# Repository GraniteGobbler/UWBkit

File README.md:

# UWBkit

This is a repository containing firmware from two other repositories and is released under their license:
- [DWM3001C-starter-firmware](https://github.com/Uberi/DWM3001C-starter-firmware), by Uberi (as of [02c341b](https://github.com/Uberi/DWM3001C-starter-firmware/commit/02c341b4f58dd8410239b5278b40aece675a3650))
- [SSD1306-LCD-on-NRF52](https://github.com/jimmywong2003/SSD1306-LCD-on-NRF52), by jimmywong2003 (as of [4ca746a](https://github.com/jimmywong2003/SSD1306-LCD-on-NRF52/commit/4ca746a075d3628c971d63ee42bb9b67d5787345))

All other files are released under the [Creative Commons CC0 license](https://creativecommons.org/public-domain/cc0/).

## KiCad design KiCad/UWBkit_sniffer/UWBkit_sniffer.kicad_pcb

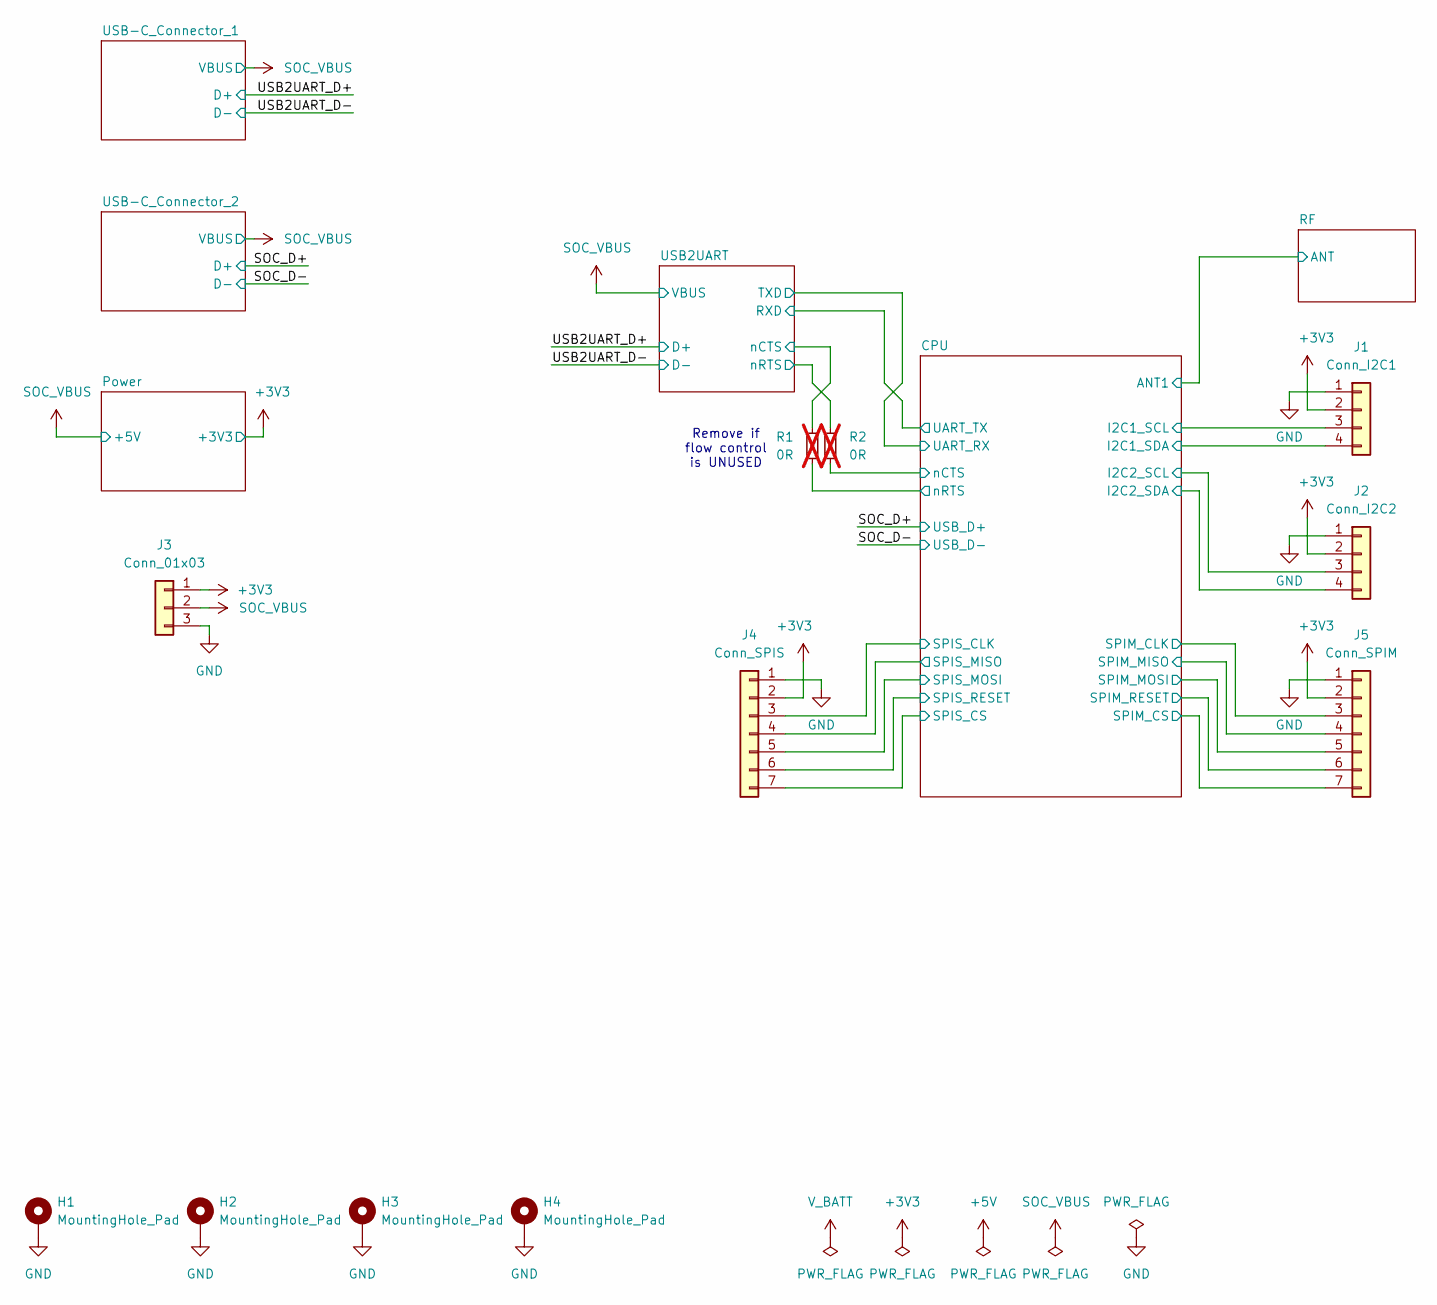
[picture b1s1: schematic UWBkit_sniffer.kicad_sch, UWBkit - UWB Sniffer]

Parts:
H1, H2, H3, H4: MountingHole_Pad; MountingHole_3.2mm_M3_Pad_Via
J1: Conn_I2C1; PinSocket_1x04_P2.54mm_Vertical
J2: Conn_I2C2; PinSocket_1x04_P2.54mm_Vertical
J3: Conn_01x03; PinSocket_1x03_P2.54mm_Vertical
J4: Conn_SPIS; PinSocket_1x07_P2.54mm_Vertical
J5: Conn_SPIM; PinSocket_1x07_P2.54mm_Vertical
R1, R2: 0R; R_0603_1608Metric; not fitted

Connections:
+3V3: J1.2, J2.2, J3.1, J4.2, J5.2; also elsewhere on the board
/CPU/I2C1_SCL: J1.3; also elsewhere on the board
/CPU/I2C1_SDA: J1.4; also elsewhere on the board
/CPU/I2C2_SCL: J2.3; also elsewhere on the board
/CPU/I2C2_SDA: J2.4; also elsewhere on the board
/CPU/SPIM_CLK: J5.3; also elsewhere on the board
/CPU/SPIM_CS: J5.7; also elsewhere on the board
/CPU/SPIM_MISO: J5.4; also elsewhere on the board
/CPU/SPIM_MOSI: J5.5; also elsewhere on the board
/CPU/SPIM_RESET: J5.6; also elsewhere on the board
/CPU/SPIS_CLK: J4.3; also elsewhere on the board
/CPU/SPIS_CS: J4.7; also elsewhere on the board
/CPU/SPIS_MISO: J4.4; also elsewhere on the board
/CPU/SPIS_MOSI: J4.5; also elsewhere on the board
/CPU/SPIS_RESET: J4.6; also elsewhere on the board
/CPU/nCTS: R2.2; also elsewhere on the board
/CPU/nRTS: R1.2; also elsewhere on the board
/USB2UART/nCTS: R1.1; also elsewhere on the board
/USB2UART/nRTS: R2.1; also elsewhere on the board
GND: H1.1, H2.1, H3.1, H4.1, J1.1, J2.1, J3.3, J4.1, J5.1; also elsewhere on the board
SOC_VBUS: J3.2; also elsewhere on the board

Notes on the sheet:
Remove if flow control is UNUSED

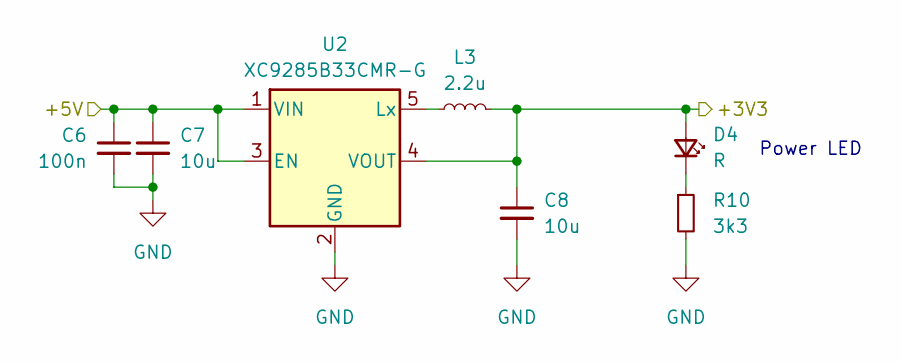
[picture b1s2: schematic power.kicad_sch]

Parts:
C6: 100n; C_0603_1608Metric
C7, C8: 10u; C_0603_1608Metric
D4: R; LED_0603_1608Metric; Voltage 1.75 V
L3: 2.2u; L_0805_2012Metric
R10: 3k3; R_0603_1608Metric
U2: XC9285B33CMR-G; SOT-23-5

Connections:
+3V3: C8.1, D4.2 (A), L3.2, U2.4 (VOUT); also elsewhere on the board
GND: C6.2, C7.2, C8.2, R10.2, U2.2 (GND); also elsewhere on the board
unnamed: D4.1 (K), R10.1
unnamed: L3.1, U2.5 (Lx)
SOC_VBUS: C6.1, C7.1, U2.1 (VIN), U2.3 (EN); also elsewhere on the board

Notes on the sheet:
Power LED

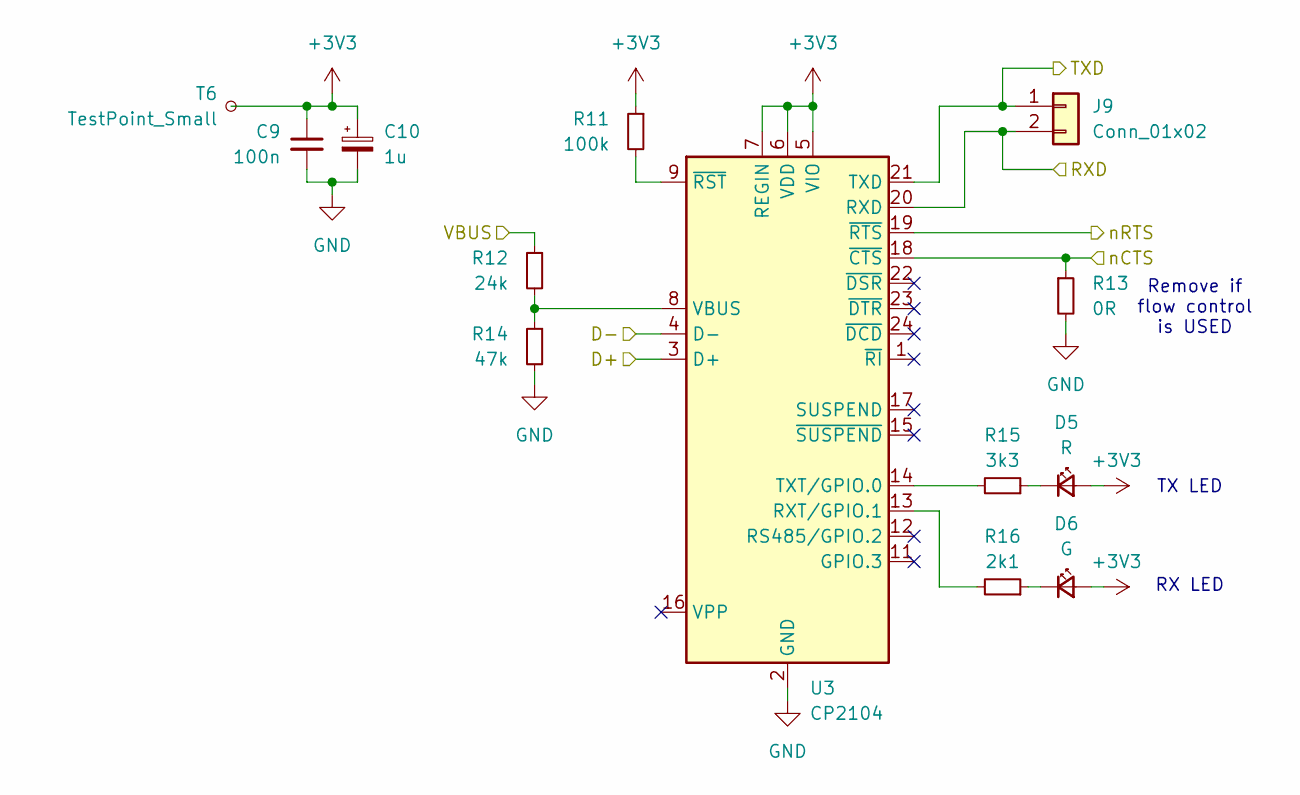
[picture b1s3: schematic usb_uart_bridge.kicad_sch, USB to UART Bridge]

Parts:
C9: 100n; C_0603_1608Metric
C10: 1u; CP_EIA-3216-18_Kemet-A
D5: R; LED_0603_1608Metric; Voltage 1.75 V
D6: G; LED_0603_1608Metric; Voltage 2.25 V
J9: Conn_01x02; PinHeader_1x02_P2.54mm_Vertical
R11: 100k; R_0603_1608Metric
R12: 24k; R_0603_1608Metric
R13: 0R; R_0603_1608Metric
R14: 47k; R_0603_1608Metric
R15: 3k3; R_0603_1608Metric
R16: 2k1; R_0603_1608Metric
T6: TestPoint_Small; TestPoint_Pad_D1.0mm
U3: CP2104; QFN-24-1EP_4x4mm_P0.5mm_EP2.6x2.6mm

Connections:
+3V3: C9.1, C10.1, D5.2 (A), D6.2 (A), R11.1, T6.1, U3.5 (VIO), U3.6 (VDD), U3.7 (REGIN); also elsewhere on the board
/CPU/UART_RX: J9.1, U3.21 (TXD); also elsewhere on the board
/CPU/UART_TX: J9.2, U3.20 (RXD); also elsewhere on the board
/USB2UART/nCTS: R13.1, U3.18 (~CTS); also elsewhere on the board
/USB2UART/nRTS: U3.19 (~RTS); also elsewhere on the board
/USB2UART_D+: U3.3 (D+); also elsewhere on the board
/USB2UART_D-: U3.4 (D-); also elsewhere on the board
GND: C9.2, C10.2, R13.2, R14.2, U3.2 (GND), U3.25 (GND); also elsewhere on the board
unnamed: D5.1 (K), R15.1
unnamed: D6.1 (K), R16.1
unnamed: R16.2, U3.13 (RXT/GPIO.1)
unnamed: R15.2, U3.14 (TXT/GPIO.0)
unnamed: R12.2, R14.1, U3.8 (VBUS)
unnamed: R11.2, U3.9 (~RST)
SOC_VBUS: R12.1; also elsewhere on the board

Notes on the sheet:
Remove if flow control is USED
TX LED
RX LED

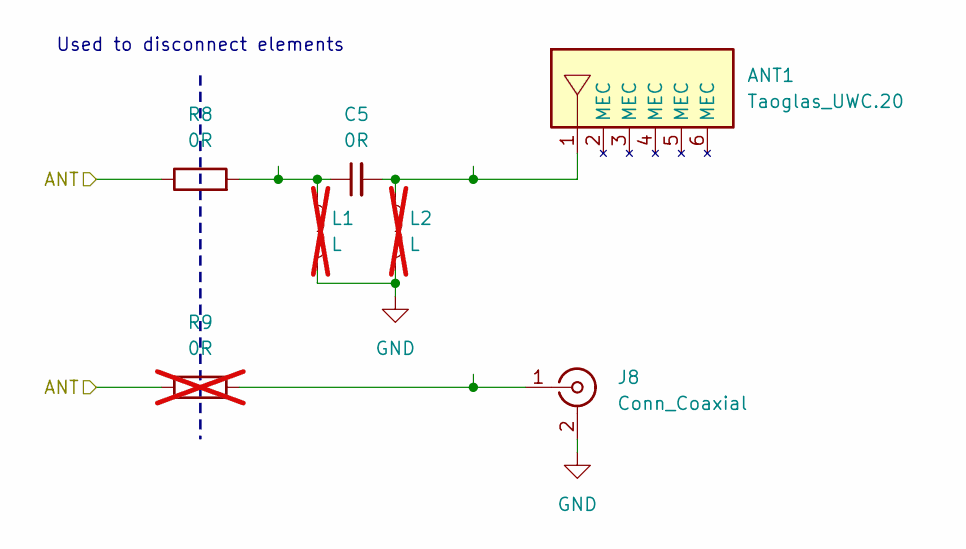
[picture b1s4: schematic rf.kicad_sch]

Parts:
ANT1: Taoglas_UWC.20
C5: 0R; C_0603_1608Metric
J8: Conn_Coaxial; SMA_Molex_73251-1153_EdgeMount_Horizontal
L1, L2: L; L_0603_1608Metric; not fitted
R8: 0R; R_0603_1608Metric
R9: 0R; R_0603_1608Metric; not fitted

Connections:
/CPU/ANT1: R8.1, R9.1; also elsewhere on the board
GND: J8.2 (Ext), L1.2, L2.2; also elsewhere on the board
unnamed: ANT1.1, C5.2, L2.1
unnamed: C5.1, L1.1, R8.2
unnamed: J8.1 (In), R9.2

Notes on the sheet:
Used to disconnect elements

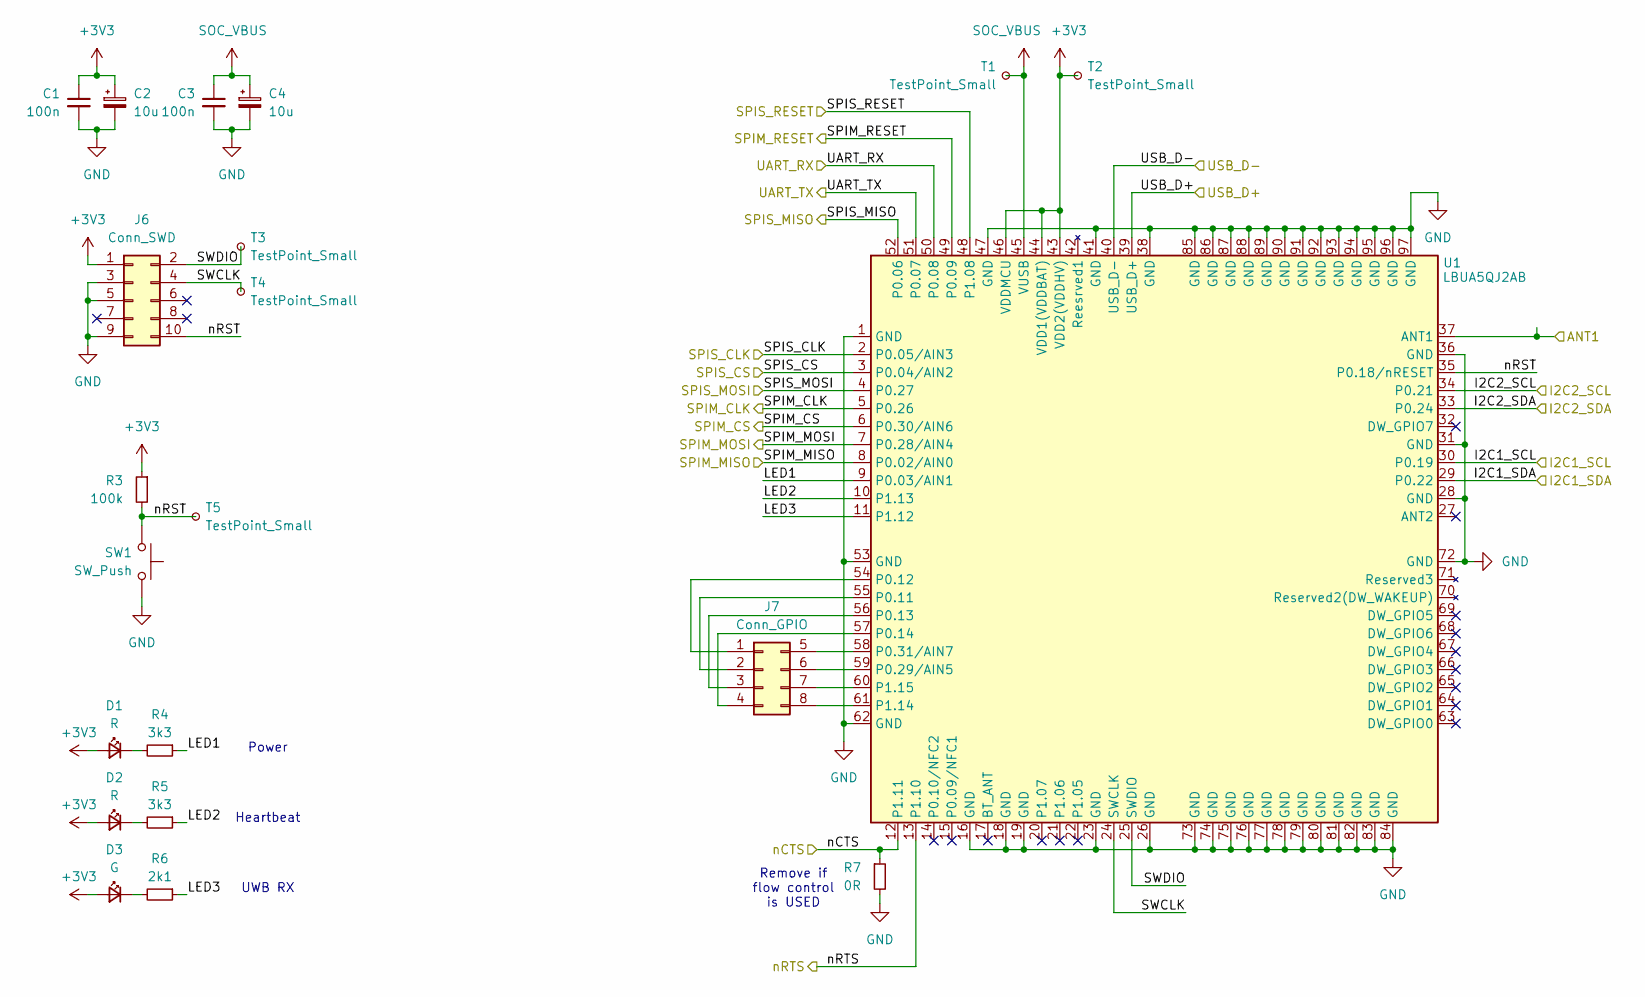
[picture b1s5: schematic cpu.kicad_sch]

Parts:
C1, C3: 100n; C_0603_1608Metric
C2, C4: 10u; CP_EIA-3216-18_Kemet-A
D1, D2: R; LED_0603_1608Metric; Voltage 1.75 V
D3: G; LED_0603_1608Metric; Voltage 2.25 V
J6: Conn_SWD; PinHeader_2x05_P1.27mm_Vertical_SMD
J7: Conn_GPIO; PinSocket_2x04_P2.54mm_Vertical
R3: 100k; R_0603_1608Metric
R4, R5: 3k3; R_0603_1608Metric
R6: 2k1; R_0603_1608Metric
R7: 0R; R_0603_1608Metric
SW1: SW_Push; SW_TH_Tactile_Omron_B3F-106x
T1, T2, T3, T4, T5: TestPoint_Small; TestPoint_Pad_D1.0mm
U1: LBUA5QJ2AB

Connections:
+3V3: C1.1, C2.1, D1.2 (A), D2.2 (A), D3.2 (A), J6.1, R3.1, T2.1, U1.43 (VDD2(VDDHV)), U1.44 (VDD1(VDDBAT)), U1.46 (VDDMCU); also elsewhere on the board
/CPU/ANT1: U1.37 (ANT1); also elsewhere on the board
/CPU/I2C1_SCL: U1.30 (P0.19); also elsewhere on the board
/CPU/I2C1_SDA: U1.29 (P0.22); also elsewhere on the board
/CPU/I2C2_SCL: U1.34 (P0.21); also elsewhere on the board
/CPU/I2C2_SDA: U1.33 (P0.24); also elsewhere on the board
/CPU/LED1: R4.1, U1.9 (P0.03/AIN1)
/CPU/LED2: R5.1, U1.10 (P1.13)
/CPU/LED3: R6.1, U1.11 (P1.12)
/CPU/SPIM_CLK: U1.5 (P0.26); also elsewhere on the board
/CPU/SPIM_CS: U1.6 (P0.30/AIN6); also elsewhere on the board
/CPU/SPIM_MISO: U1.8 (P0.02/AIN0); also elsewhere on the board
/CPU/SPIM_MOSI: U1.7 (P0.28/AIN4); also elsewhere on the board
/CPU/SPIM_RESET: U1.49 (P0.09); also elsewhere on the board
/CPU/SPIS_CLK: U1.2 (P0.05/AIN3); also elsewhere on the board
/CPU/SPIS_CS: U1.3 (P0.04/AIN2); also elsewhere on the board
/CPU/SPIS_MISO: U1.52 (P0.06); also elsewhere on the board
/CPU/SPIS_MOSI: U1.4 (P0.27); also elsewhere on the board
/CPU/SPIS_RESET: U1.48 (P1.08); also elsewhere on the board
/CPU/SWCLK: J6.4, T4.1, U1.24 (SWCLK)
/CPU/SWDIO: J6.2, T3.1, U1.25 (SWDIO)
/CPU/UART_RX: U1.50 (P0.08); also elsewhere on the board
/CPU/UART_TX: U1.51 (P0.07); also elsewhere on the board
/CPU/nCTS: R7.1, U1.12 (P1.11); also elsewhere on the board
/CPU/nRST: J6.10, R3.2, SW1.2, T5.1, U1.35 (P0.18/nRESET)
/CPU/nRTS: U1.13 (P1.10); also elsewhere on the board
/SOC_D+: U1.39 (USB_D+); also elsewhere on the board
/SOC_D-: U1.40 (USB_D-); also elsewhere on the board
GND: C1.2, C2.2, C3.2, C4.2, J6.3, J6.5, J6.9, R7.2, SW1.1, U1.1 (GND), U1.16 (GND), U1.18 (GND), U1.19 (GND), U1.23 (GND), U1.26 (GND), U1.28 (GND), U1.31 (GND), U1.36 (GND), U1.38 (GND), U1.41 (GND), U1.47 (GND), U1.53 (GND), U1.62 (GND), U1.72 (GND), U1.73 (GND), U1.74 (GND), U1.75 (GND), U1.76 (GND), U1.77 (GND), U1.78 (GND), U1.79 (GND), U1.80 (GND), U1.81 (GND), U1.82 (GND), U1.83 (GND), U1.84 (GND), U1.85 (GND), U1.86 (GND), U1.87 (GND), U1.88 (GND), U1.89 (GND), U1.90 (GND), U1.91 (GND), U1.92 (GND), U1.93 (GND), U1.94 (GND), U1.95 (GND), U1.96 (GND), U1.97 (GND); also elsewhere on the board
unnamed: D1.1 (K), R4.2
unnamed: D2.1 (K), R5.2
unnamed: D3.1 (K), R6.2
unnamed: J7.1, U1.54 (P0.12)
unnamed: J7.2, U1.55 (P0.11)
unnamed: J7.3, U1.56 (P0.13)
unnamed: J7.4, U1.57 (P0.14)
unnamed: J7.5, U1.58 (P0.31/AIN7)
unnamed: J7.6, U1.59 (P0.29/AIN5)
unnamed: J7.7, U1.60 (P1.15)
unnamed: J7.8, U1.61 (P1.14)
SOC_VBUS: C3.1, C4.1, T1.1, U1.45 (VUSB); also elsewhere on the board

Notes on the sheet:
Power
Heartbeat
Remove if flow control is USED
UWB RX

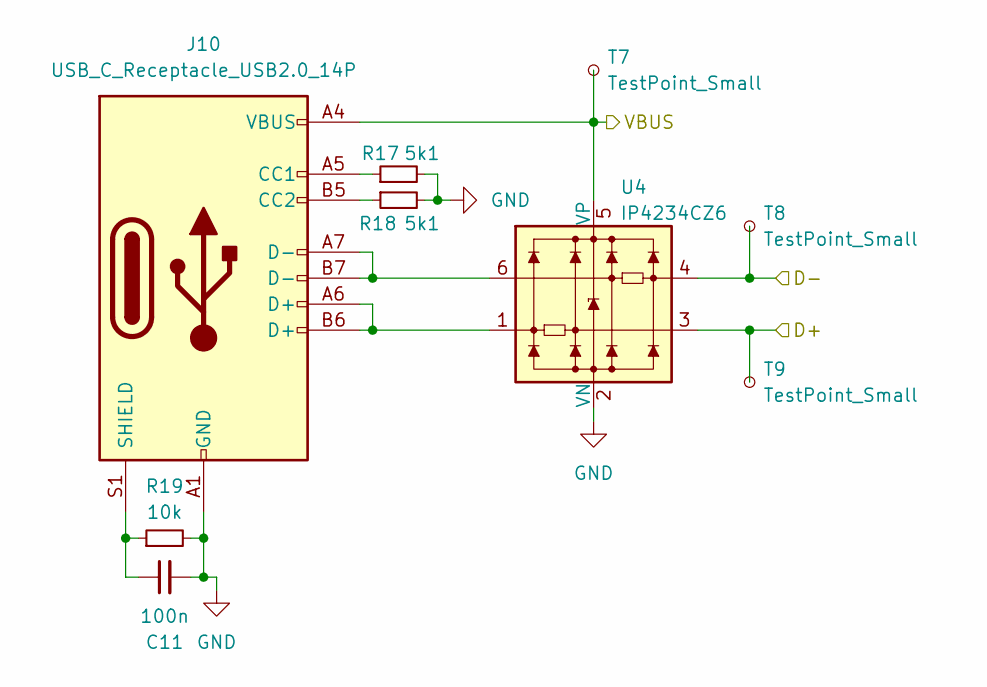
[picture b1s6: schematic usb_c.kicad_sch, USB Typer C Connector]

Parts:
C11: 100n; C_0603_1608Metric
J10: USB_C_Receptacle_USB2.0_14P; USB_C_Receptacle_GCT_USB4105-xx-A_16P_TopMnt_Horizontal
R17, R18: 5k1; R_0603_1608Metric
R19: 10k; R_0603_1608Metric
T7, T8, T9: TestPoint_Small; TestPoint_Pad_D1.0mm
U4: IP4234CZ6; SC-74-6_1.55x2.9mm_P0.95mm

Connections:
/USB2UART_D+: T9.1, U4.3; also elsewhere on the board
/USB2UART_D-: T8.1, U4.4; also elsewhere on the board
GND: C11.2, J10.A1 (GND), J10.A12 (GND), J10.B1 (GND), J10.B12 (GND), R17.2, R18.2, R19.2, U4.2 (VN); also elsewhere on the board
unnamed: J10.A5 (CC1), R17.1
unnamed: J10.B5 (CC2), R18.1
unnamed: J10.A6 (D+), J10.B6 (D+), U4.1
unnamed: J10.A7 (D-), J10.B7 (D-), U4.6
unnamed: C11.1, J10.S1 (SHIELD), R19.1
SOC_VBUS: J10.A4 (VBUS), J10.A9 (VBUS), J10.B4 (VBUS), J10.B9 (VBUS), T7.1, U4.5 (VP); also elsewhere on the board

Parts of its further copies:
C12: 100n; C_0603_1608Metric
J11: USB_C_Receptacle_USB2.0_14P; USB_C_Receptacle_GCT_USB4105-xx-A_16P_TopMnt_Horizontal
R20, R21: 5k1; R_0603_1608Metric
R22: 10k; R_0603_1608Metric
T10, T11, T12: TestPoint_Small; TestPoint_Pad_D1.0mm
U5: IP4234CZ6; SC-74-6_1.55x2.9mm_P0.95mm

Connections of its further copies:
/SOC_D+: T12.1, U5.3; also elsewhere on the board
/SOC_D-: T11.1, U5.4; also elsewhere on the board
GND: C12.2, J11.A1 (GND), J11.A12 (GND), J11.B1 (GND), J11.B12 (GND), R20.2, R21.2, R22.2, U5.2 (VN); also elsewhere on the board
unnamed: J11.A5 (CC1), R20.1
unnamed: J11.B5 (CC2), R21.1
unnamed: J11.A6 (D+), J11.B6 (D+), U5.1
unnamed: J11.A7 (D-), J11.B7 (D-), U5.6
unnamed: C12.1, J11.S1 (SHIELD), R22.1
SOC_VBUS: J11.A4 (VBUS), J11.A9 (VBUS), J11.B4 (VBUS), J11.B9 (VBUS), T10.1, U5.5 (VP); also elsewhere on the board

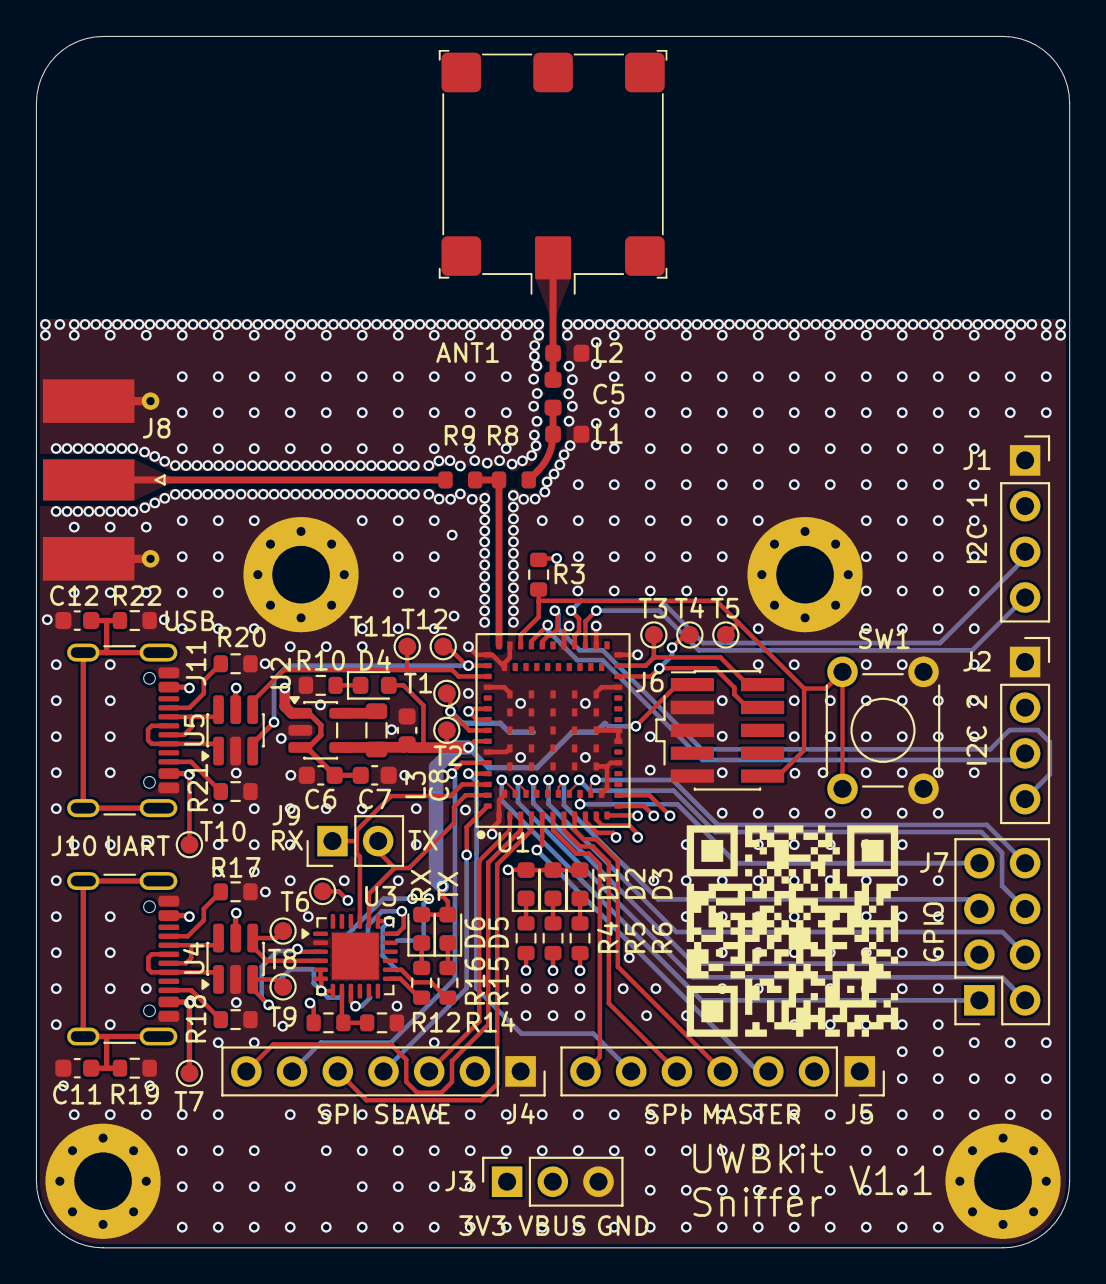
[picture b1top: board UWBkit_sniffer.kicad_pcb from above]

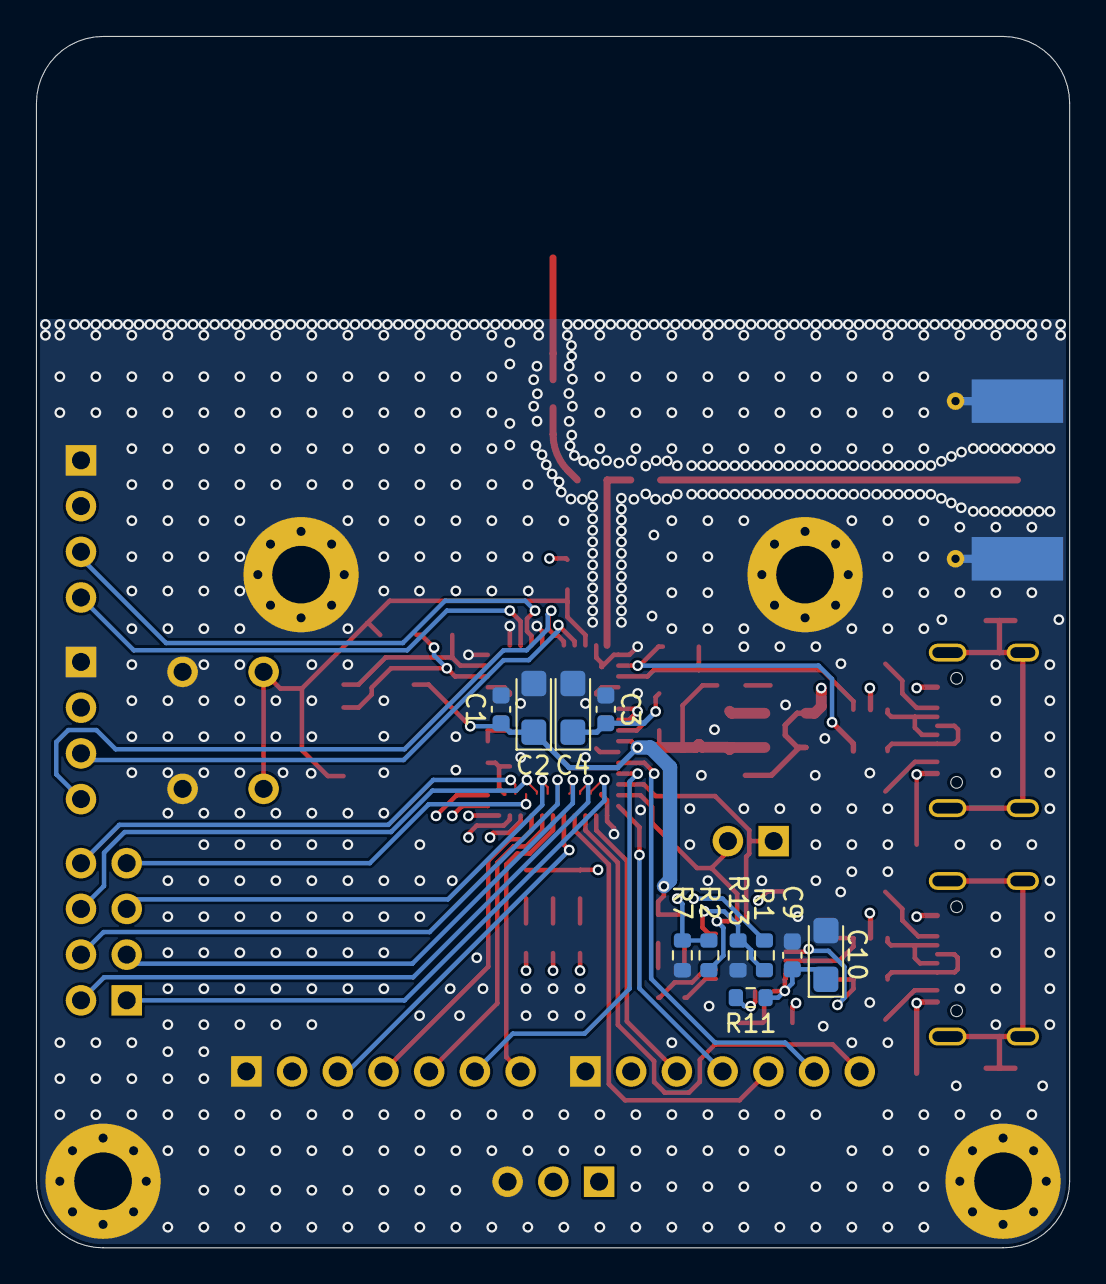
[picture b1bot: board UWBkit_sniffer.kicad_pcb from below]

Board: 4 copper layers, 57.4 x 67.3 mm, 78 parts (11 on the bottom side), 66 nets.

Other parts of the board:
QR*****: https://github.com/GraniteGobbler/UWBkit; Git-Repo-QR

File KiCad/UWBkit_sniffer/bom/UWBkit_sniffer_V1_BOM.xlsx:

Reference | Qty | Qty Owned | Qty Need | Value | Footprint |  | Mouser link
ANT1 | 1 | 0 | 1 | Taoglas_UWC.20 | UWB_Antennas:Taoglas_UWC.20 | https://cz.mouser.com/ProductDetail/Taoglas/UWC.20?qs=MLItCL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 | https://cz.mouser.com/ProductDetail/Taoglas/UWC.20?qs=MLItCL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
C1,C3,C6,C9,C11,C12 | 6 | 6 | 0 | 100n | Capacitor_SMD:C_0603_1608Metric
C2,C4 | 2 | 8 | -6 | 10u | Capacitor_Tantalum_SMD:CP_EIA-3216-18_Kemet-A
C5 | 1 | 0 | 1 | 0R | Capacitor_SMD:C_0603_1608Metric | https://cz.mouser.com/ProductDetail/Panasonic/ERJ-H3G0R00V?q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 | https://cz.mouser.com/ProductDetail/Panasonic/ERJ-H3G0R00V?q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
C7,C8 | 2 | 6 | -4 | 10u | Capacitor_SMD:C_0603_1608Metric
C10 | 1 | 0 | 1 | 1u | Capacitor_Tantalum_SMD:CP_EIA-3216-18_Kemet-A | https://cz.mouser.com/ProductDetail/KEMET/T491A105K020ATAUTO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 | https://cz.mouser.com/ProductDetail/KEMET/T491A105K020ATAUTO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
D1,D2,D4,D5 | 4 | 4 | 0 | R | LED_SMD:LED_0603_1608Metric
D3,D6 | 2 | 2 | 0 | G | LED_SMD:LED_0603_1608Metric
H1,H2,H3,H4 | 4 | 4 | 0 | MountingHole_Pad | MountingHole:MountingHole_3.2mm_M3_Pad_Via
J1 | 1 | 1 | 0 | Conn_I2C1 | Connector_PinSocket_2.54mm:PinSocket_1x04_P2.54mm_Vertical
J2 | 1 | 1 | 0 | Conn_I2C2 | Connector_PinSocket_2.54mm:PinSocket_1x04_P2.54mm_Vertical
J3 | 1 | 1 | 0 | Conn_01x03 | Connector_PinSocket_2.54mm:PinSocket_1x03_P2.54mm_Vertical
J4 | 1 | 1 | 0 | Conn_SPIS | Connector_PinSocket_2.54mm:PinSocket_1x07_P2.54mm_Vertical
J5 | 1 | 1 | 0 | Conn_SPIM | Connector_PinSocket_2.54mm:PinSocket_1x07_P2.54mm_Vertical
J6 | 1 | 0 | 1 | Conn_SWD | Connector_PinHeader_1.27mm:PinHeader_2x05_P1.27mm_Vertical_SMD | https://cz.mouser.com/ProductDetail/Samtec/FTSH-105-01-F-DV-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 | https://cz.mouser.com/ProductDetail/Samtec/FTSH-105-01-F-DV-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
J7 | 1 | 1 | 0 | Conn_GPIO | Connector_PinSocket_2.54mm:PinSocket_2x04_P2.54mm_Vertical
J8 | 1 | 0 | 1 | Conn_Coaxial | Connector_Coaxial:SMA_Molex_73251-1153_EdgeMount_Horizontal | https://cz.mouser.com/ProductDetail/Molex/73251-1153?qs=vxeU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 | https://cz.mouser.com/ProductDetail/Molex/73251-1153?qs=vxeU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
J9 | 1 | 1 | 0 | Conn_01x02 | Connector_PinHeader_2.54mm:PinHeader_1x02_P2.54mm_Vertical
J10,J11 | 2 | 1 | 1 | USB_C_Receptacle_USB2.0_14P | Connector_USB:USB_C_Receptacle_GCT_USB4105-xx-A_16P_TopMnt_Horizontal | https://cz.mouser.com/ProductDetail/GCT/USB4105-GF-A?qs=KUoI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 | https://cz.mouser.com/ProductDetail/GCT/USB4105-GF-A?qs=KUoI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
L1,L2 (DNP) | 2 | 2 | 0 | L | Inductor_SMD:L_0603_1608Metric
L3 | 1 | 8 | -7 | 2.2u | Inductor_SMD:L_0805_2012Metric
R1,R2,R9 (DNP) | 3 | 3 | 0 | 0R | Resistor_SMD:R_0603_1608Metric
R3,R11 | 2 | 15 | -13 | 100k | Resistor_SMD:R_0603_1608Metric
R4,R5,R10,R15 | 4 | 0 | 4 | 3k3 | Resistor_SMD:R_0603_1608Metric | https://cz.mouser.com/ProductDetail/YAGEO/RC0603FR-073K3L?qs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 | https://cz.mouser.com/ProductDetail/YAGEO/RC0603FR-073K3L?qs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
R6,R16 | 2 | 0 | 2 | 2k1 | Resistor_SMD:R_0603_1608Metric | https://cz.mouser.com/ProductDetail/YAGEO/RC0603FR-072K1L?qs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 | https://cz.mouser.com/ProductDetail/YAGEO/RC0603FR-072K1L?qs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
R7,R8,R13 | 3 | 3 | 0 | 0R | Resistor_SMD:R_0603_1608Metric
R12 | 1 | 0 | 1 | 24k | Resistor_SMD:R_0603_1608Metric | https://cz.mouser.com/ProductDetail/YAGEO/RC0603FR-1024KL?qs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 | https://cz.mouser.com/ProductDetail/YAGEO/RC0603FR-1024KL?qs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
R14 | 1 | 0 | 1 | 47k | Resistor_SMD:R_0603_1608Metric | https://cz.mouser.com/ProductDetail/YAGEO/AC0603FR-1347KL?qs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 | https://cz.mouser.com/ProductDetail/YAGEO/AC0603FR-1347KL?qs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
R17,R18,R20,R21 | 4 | 6 | -2 | 5k1 | Resistor_SMD:R_0603_1608Metric
R19,R22 | 2 | 8 | -6 | 10k | Resistor_SMD:R_0603_1608Metric
SW1 | 1 | 1 | 0 | SW_Push | Button_Switch_THT:SW_TH_Tactile_Omron_B3F-106x
U1 | 1 | 0 | 1 | LBUA5QJ2AB | LBUA5QJ2AB:LBUA5QJ2AB | https://cz.mouser.com/ProductDetail/Murata/LBUA5QJ2AB-828?qs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 | https://cz.mouser.com/ProductDetail/Murata/LBUA5QJ2AB-828?qs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
U2 | 1 | 0 | 1 | XC9285B33CMR-G | Package_TO_SOT_SMD:SOT-23-5 | https://cz.mouser.com/ProductDetail/Torex-Semiconductor/XC92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 | https://cz.mouser.com/ProductDetail/Torex-Semiconductor/XC92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
U3 | 1 | 0 | 1 | CP2104 | Package_DFN_QFN:QFN-24-1EP_4x4mm_P0.5mm_EP2.6x2.6mm | https://cz.mouser.com/ProductDetail/Silicon-Labs/CP2104-F03-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 | https://cz.mouser.com/ProductDetail/Silicon-Labs/CP2104-F03-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
U4,U5 | 2 | 1 | 1 | IP4234CZ6 | Package_TO_SOT_SMD:SC-74-6_1.55x2.9mm_P0.95mm | https://cz.mouser.com/ProductDetail/STMicroelectronics/USBLC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 | https://cz.mouser.com/ProductDetail/STMicroelectronics/USBLC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
0R |  |  | 7

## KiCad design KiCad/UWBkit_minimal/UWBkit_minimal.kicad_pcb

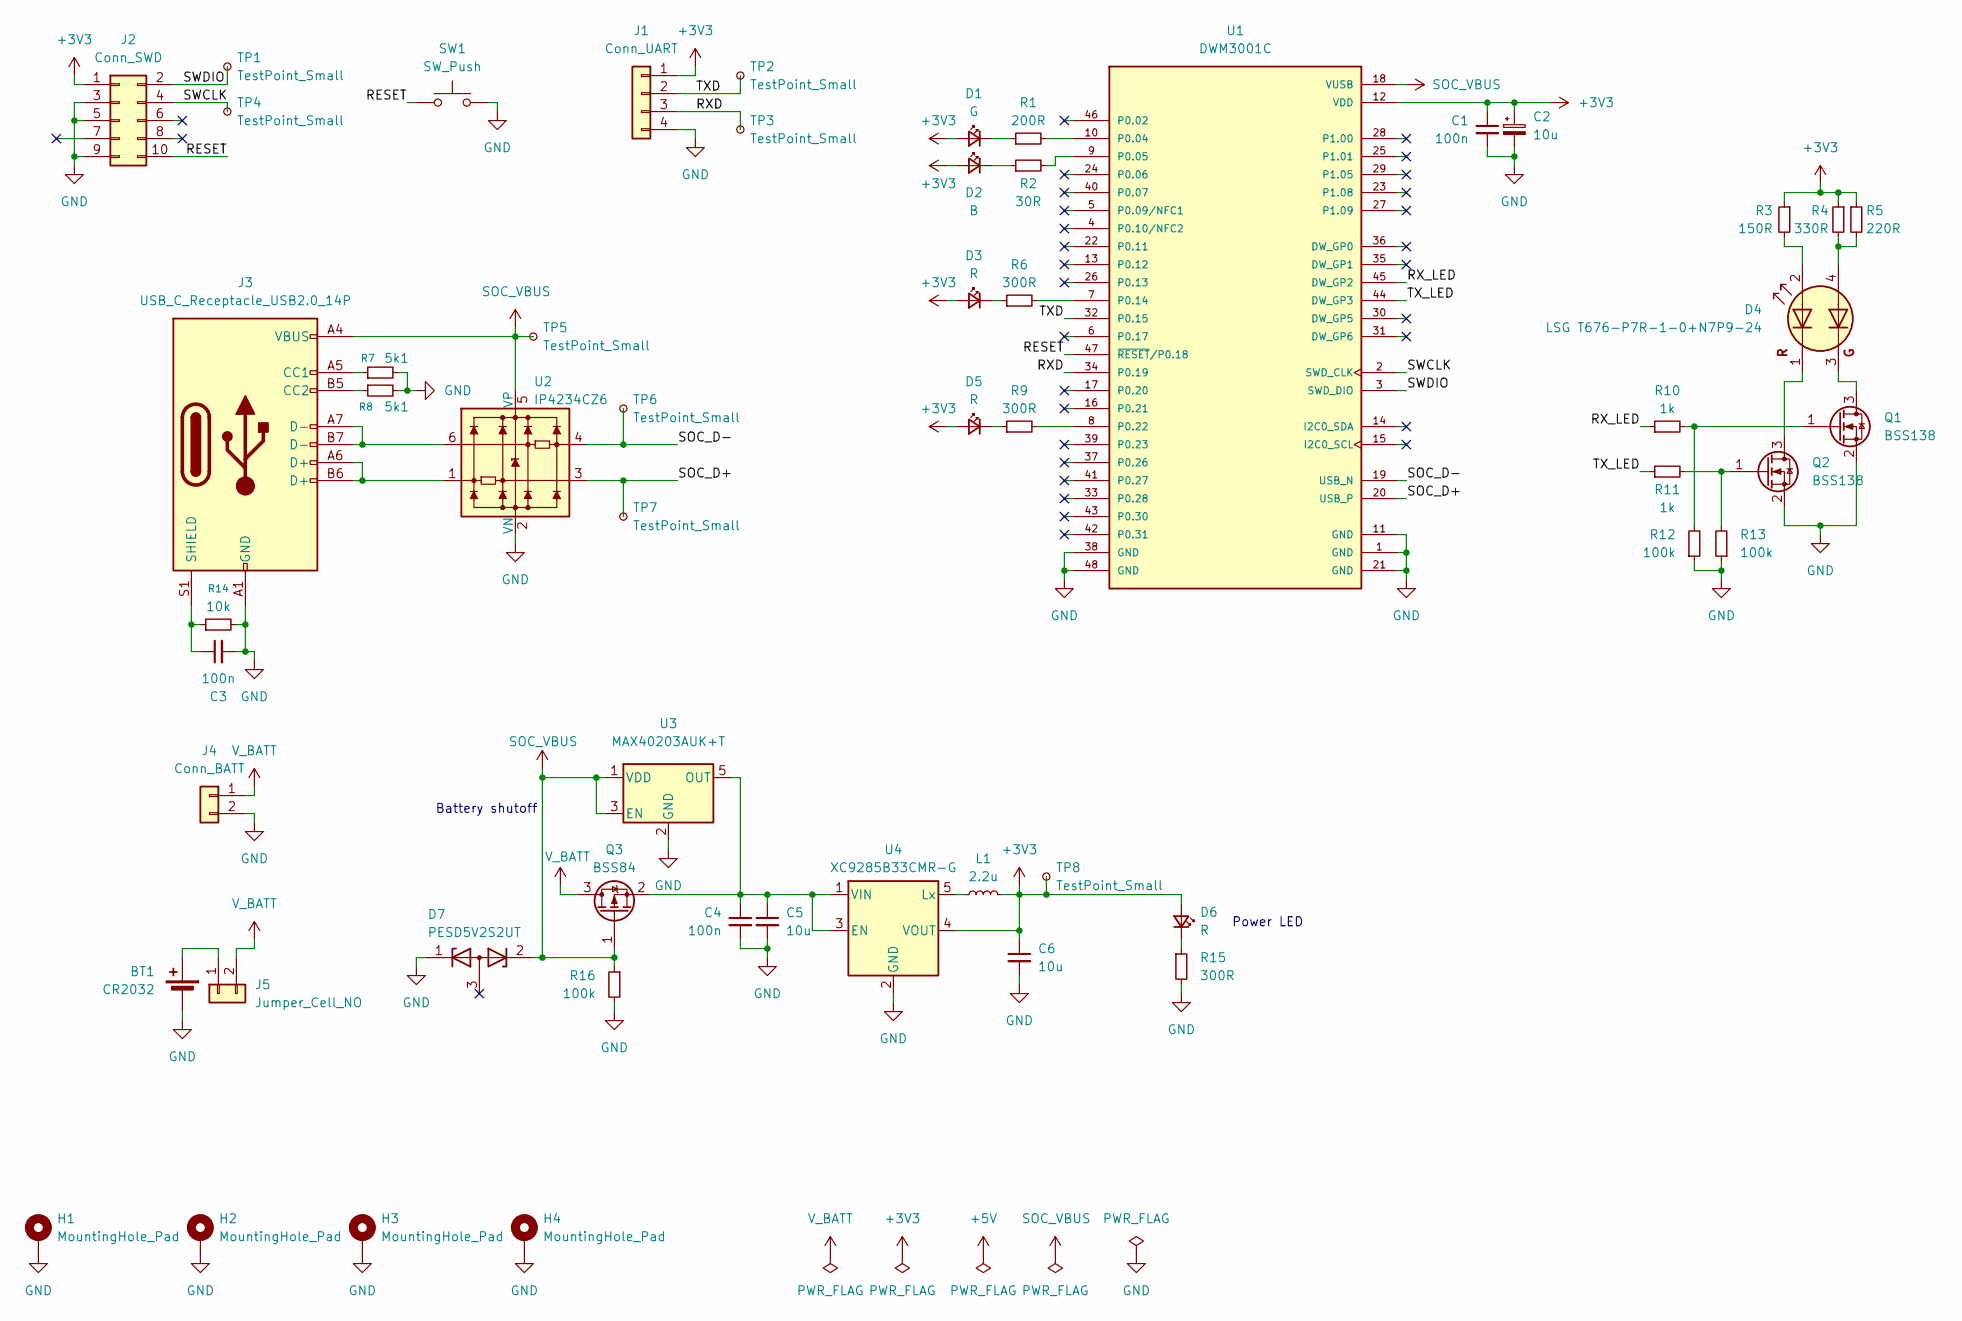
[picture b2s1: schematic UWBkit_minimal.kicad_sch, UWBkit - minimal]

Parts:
BT1: CR2032; BatteryHolder_Keystone_1058_1x2032
C1, C3, C4: 100n; C_0603_1608Metric
C2: 10u; CP_EIA-3216-18_Kemet-A
C5, C6: 10u; C_0603_1608Metric
D1: G; LED_0603_1608Metric
D2: B; LED_0603_1608Metric
D3, D5, D6: R; LED_0603_1608Metric
D4: LSG T676-P7R-1-0+N7P9-24; LED_Dual_OSRAM-PLCC4_3.2x2.8mm
D7: PESD5V2S2UT; SOT-23
H1, H2, H3, H4: MountingHole_Pad; MountingHole_3.2mm_M3_ISO14580_Pad_TopBottom
J1: Conn_UART; PinSocket_1x04_P2.54mm_Vertical
J2: Conn_SWD; PinHeader_2x05_P1.27mm_Vertical_SMD
J3: USB_C_Receptacle_USB2.0_14P; USB_C_Receptacle_GCT_USB4105-xx-A_16P_TopMnt_Horizontal
J4: Conn_BATT; PinSocket_1x02_P2.54mm_Vertical
J5: Jumper_Cell_NO; PinHeader_1x02_P2.54mm_Vertical
L1: 2.2u; L_0805_2012Metric
Q1, Q2: BSS138; SOT-23
Q3: BSS84; SOT-23-3
R1: 200R; R_0603_1608Metric
R2: 30R; R_0603_1608Metric
R3: 150R; R_0603_1608Metric
R4: 330R; R_0603_1608Metric
R5: 220R; R_0603_1608Metric
R6, R9, R15: 300R; R_0603_1608Metric
R7, R8: 5k1; R_0603_1608Metric
R10, R11: 1k; R_0603_1608Metric
R12, R13, R16: 100k; R_0603_1608Metric
R14: 10k; R_0603_1608Metric
SW1: SW_Push; SW_TH_Tactile_Omron_B3F-106x
TP1, TP4: TestPoint_Small; TestPoint_Pad_D1.5mm
TP2, TP3, TP5, TP6, TP7, TP8: TestPoint_Small; TestPoint_Pad_D1.0mm
U1: DWM3001C; PARTREV Rev C
U2: IP4234CZ6; SC-74-6_1.55x2.9mm_P0.95mm
U3: MAX40203AUK+T; SOT-23-5
U4: XC9285B33CMR-G; SOT-23-5

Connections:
+3V3: C1.1, C2.1, C6.1, D1.2 (A), D2.2 (A), D3.2 (A), D5.2 (A), D6.2 (A), J1.1, J2.1, L1.2, R3.1, R4.1, R5.1, TP8.1, U1.12 (VDD), U4.4 (VOUT)
/RESET: J2.10, SW1.2, U1.47 (~RESET/P0.18)
/RXD: J1.3, TP3.1, U1.34 (P0.19)
/RX_LED: R10.1, U1.45 (DW_GP2)
/SOC_D+: TP7.1, U1.20 (USB_P), U2.3
/SOC_D-: TP6.1, U1.19 (USB_N), U2.4
/SWCLK: J2.4, TP4.1, U1.2 (SWD_CLK)
/SWDIO: J2.2, TP1.1, U1.3 (SWD_DIO)
/TXD: J1.2, TP2.1, U1.32 (P0.15)
/TX_LED: R11.1, U1.44 (DW_GP3)
GND: BT1.2 (-), C1.2, C2.2, C3.2, C4.2, C5.2, C6.2, D7.1 (K), H1.1, H2.1, H3.1, H4.1, J1.4, J2.3, J2.5, J2.9, J3.A1 (GND), J3.A12 (GND), J3.B1 (GND), J3.B12 (GND), J4.2, Q1.2 (S), Q2.2 (S), R7.2, R8.2, R12.1, R13.1, R14.2, R15.2, R16.2, SW1.1, U1.1 (GND), U1.11 (GND), U1.21 (GND), U1.38 (GND), U1.48 (GND), U2.2 (VN), U3.2 (GND), U4.2 (GND)
unnamed: BT1.1 (+), J5.1
unnamed: D1.1 (K), R1.1
unnamed: D2.1 (K), R2.1
unnamed: D3.1 (K), R6.1
unnamed: D4.2 (A1), R3.2
unnamed: D4.4 (A2), R4.2, R5.2
unnamed: D4.1 (K1), Q2.3 (D)
unnamed: D4.3 (K2), Q1.3 (D)
unnamed: D5.1 (K), R9.1
unnamed: D6.1 (K), R15.1
unnamed: J3.A5 (CC1), R7.1
unnamed: J3.B5 (CC2), R8.1
unnamed: J3.A6 (D+), J3.B6 (D+), U2.1
unnamed: J3.A7 (D-), J3.B7 (D-), U2.6
unnamed: C3.1, J3.S1 (SHIELD), R14.1
unnamed: Q1.1 (G), R10.2, R12.2
unnamed: Q2.1 (G), R11.2, R13.2
unnamed: C4.1, C5.1, Q3.2 (S), U3.5 (OUT), U4.1 (VIN), U4.3 (EN)
unnamed: R1.2, U1.10 (P0.04)
unnamed: R2.2, U1.9 (P0.05)
unnamed: R6.2, U1.7 (P0.14)
unnamed: R9.2, U1.8 (P0.22)
unnamed: L1.1, U4.5 (Lx)
SOC_VBUS: D7.2 (K), J3.A4 (VBUS), J3.A9 (VBUS), J3.B4 (VBUS), J3.B9 (VBUS), Q3.1 (G), R16.1, TP5.1, U1.18 (VUSB), U2.5 (VP), U3.1 (VDD), U3.3 (EN)
V_BATT: J4.1, J5.2, Q3.3 (D)

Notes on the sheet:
Battery shutoff
Power LED
